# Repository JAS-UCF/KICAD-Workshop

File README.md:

# JAS WORKSHOP - KICAD

The folders in here are the JAS -KiCAD Workshop files for a basic template, the example goes through component selection & wiring

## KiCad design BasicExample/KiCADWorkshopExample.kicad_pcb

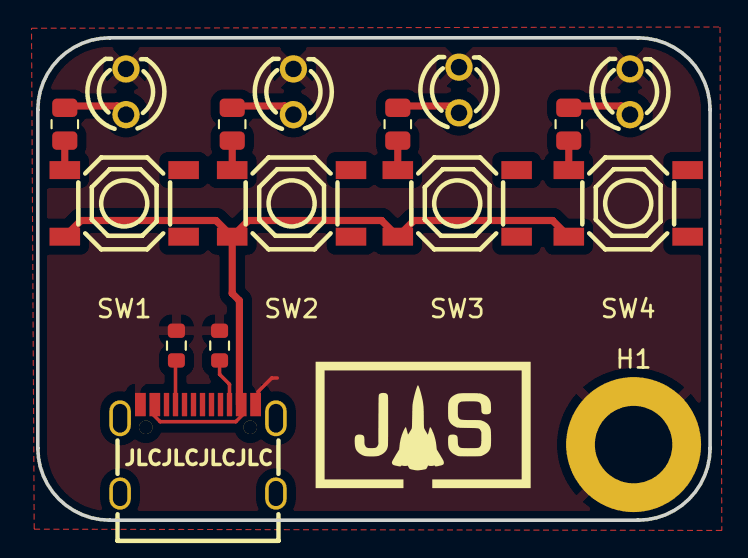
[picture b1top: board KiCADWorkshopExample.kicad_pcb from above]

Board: 2 copper layers, 37.3 x 26.8 mm, 16 parts (0 on the bottom side), 12 nets.

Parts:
H1: MountingHole_Pad; MountingHole_4.3mm_M4_DIN965_Pad
LED1, LED2, LED3, LED4: 204-10SURD/S530-A3-L; LED-TH_BD3.0-P2.54-FD
R1, R2, R3, R4: 120; R_0805_2012Metric
R5, R6: 5K1; R_0603_1608Metric
SW1, SW2, SW3, SW4: TS-1187A-B-A-B; SW-SMD_4P-L5.1-W5.1-P3.70-LS6.5-TL-2
USBC1: TYPE-C-31-M-12; USB-C_SMD-TYPE-C-31-M-12

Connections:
GND: H1.1, LED1.2 (K), LED2.2 (K), LED3.2 (K), LED4.2 (K), R5.2, R6.2, USBC1.A1 (GND), USBC1.A12 (GND), USBC1.B1 (GND), USBC1.B12 (GND)
unnamed: LED1.1 (A), R1.2
unnamed: LED2.1 (A), R2.2
unnamed: LED3.1 (A), R3.2
unnamed: LED4.1 (A), R4.2
unnamed: R4.1, SW1.4 (D)
unnamed: R3.1, SW2.4 (D)
unnamed: R2.1, SW3.4 (D)
unnamed: R1.1, SW4.4 (D)
unnamed: R6.1, USBC1.A5 (CC1)
unnamed: R5.1, USBC1.B5 (CC2)
VBUS: SW1.2 (B), SW2.2 (B), SW3.2 (B), SW4.2 (B), USBC1.A4 (VBUS), USBC1.A9 (VBUS), USBC1.B4 (VBUS), USBC1.B9 (VBUS)

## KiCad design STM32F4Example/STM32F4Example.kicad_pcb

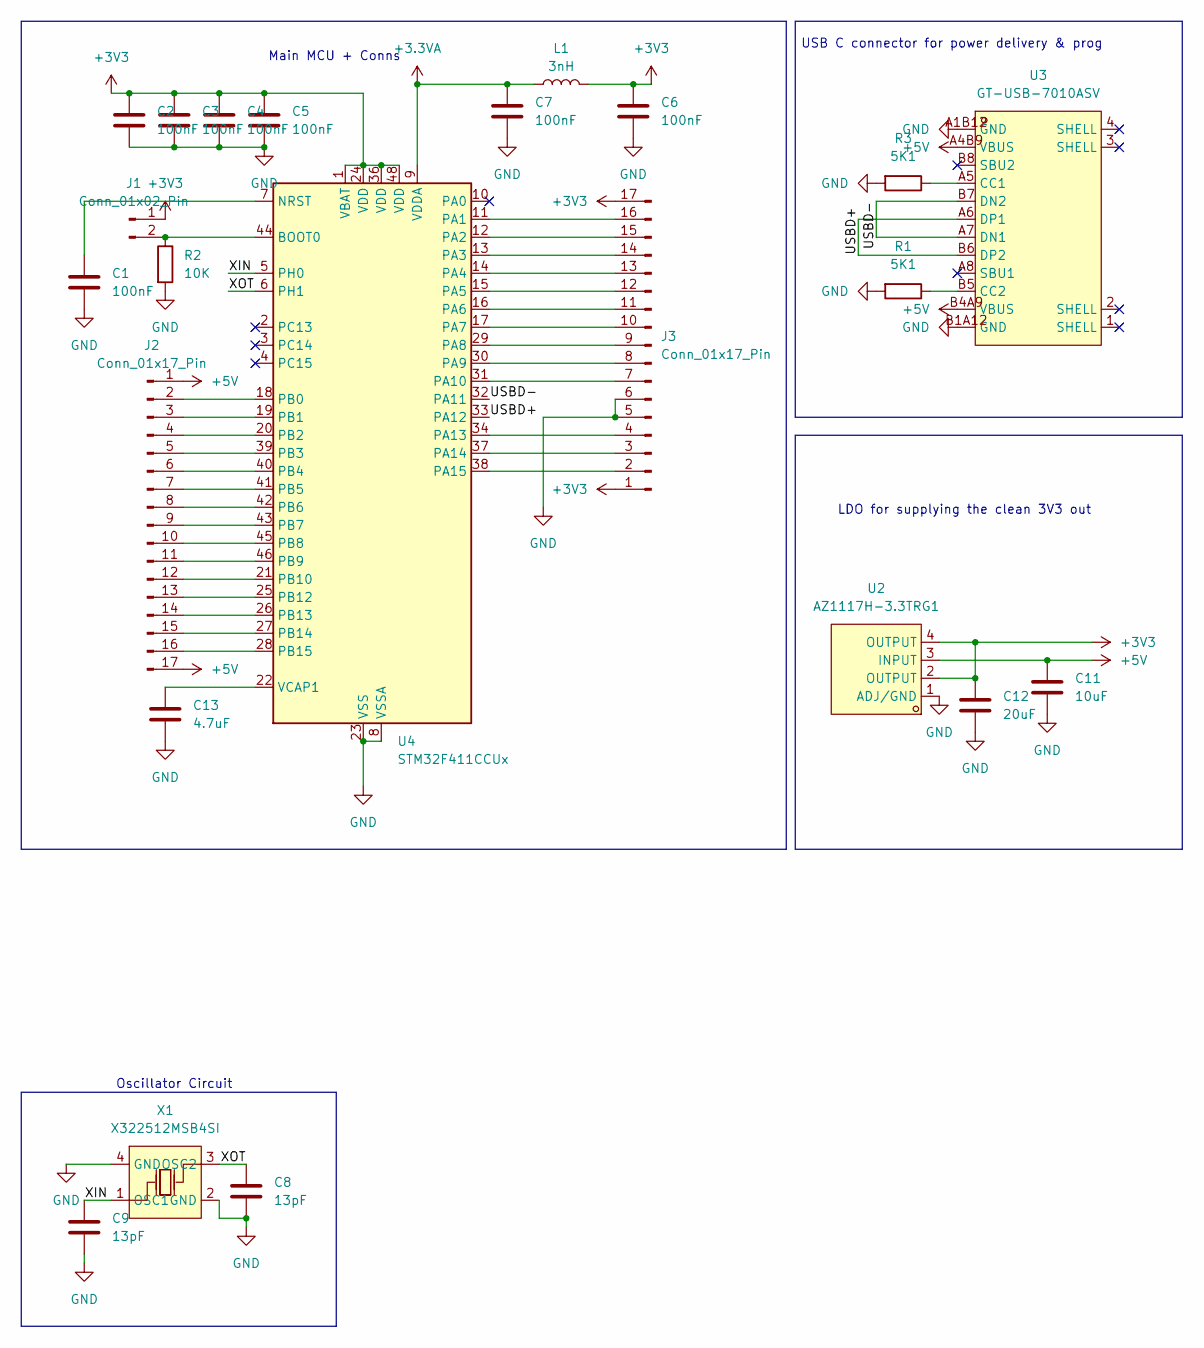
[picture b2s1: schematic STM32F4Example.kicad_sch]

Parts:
C1, C2, C3, C4, C5, C6, C7: 100nF; C_0402_1005Metric
C8, C9: 13pF; C_0402_1005Metric
C11: 10uF; C_0402_1005Metric
C12: 20uF; C_0402_1005Metric
C13: 4.7uF; C_0402_1005Metric
J1: Conn_01x02_Pin; PinHeader_1x02_P2.54mm_Vertical
J2, J3: Conn_01x17_Pin; PinHeader_1x17_P2.54mm_Vertical
L1: 3nH; L_0603_1608Metric
R1, R3: 5K1; R_0603_1608Metric
R2: 10K; R_0603_1608Metric
U2: AZ1117H-3.3TRG1; SOT-223-3_L6.5-W3.4-P2.30-LS7.0-BR; LCSC Part C110474
U3: GT-USB-7010ASV; USB-C-SMD_G-SWITCH_GT-USB-7010ASV; LCSC Part C2988369
U4: STM32F411CCUx; QFN-48-1EP_7x7mm_P0.5mm_EP5.6x5.6mm
X1: X322512MSB4SI; CRYSTAL-SMD_4P-L3.2-W2.5-BL; LCSC Part C9002

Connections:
+3.3VA: C7.1, L1.1, U4.9 (VDDA)
+3V3: C2.1, C3.1, C4.1, C5.1, C6.1, C12.1, J1.1, J3.1, J3.17, L1.2, U2.2 (OUTPUT), U2.4 (OUTPUT), U4.1 (VBAT), U4.24 (VDD), U4.36 (VDD), U4.48 (VDD); also elsewhere on the board
+5V: C11.1, J2.1, J2.17, U2.3 (INPUT), U3.A4B9 (VBUS), U3.B4A9 (VBUS)
/USBD+: U3.A6 (DP1), U3.B6 (DP2), U4.33 (PA12)
/USBD-: U3.A7 (DN1), U3.B7 (DN2), U4.32 (PA11)
/XIN: C9.1, U4.5 (PH0), X1.1 (OSC1)
/XOT: C8.1, U4.6 (PH1), X1.3 (OSC2)
GND: C1.2, C2.2, C3.2, C4.2, C5.2, C6.2, C7.2, C8.2, C9.2, C11.2, C12.2, C13.2, J3.5, J3.6, R1.2, R2.2, R3.2, U2.1 (ADJ/GND), U3.A1B12 (GND), U3.B1A12 (GND), U4.8 (VSSA), U4.23 (VSS), U4.35 (VSS), U4.47 (VSS), U4.49 (VSS), X1.2 (GND), X1.4 (GND); also elsewhere on the board
unnamed: J1.2, R2.1, U4.44 (BOOT0)
unnamed: J2.2, U4.18 (PB0)
unnamed: J2.3, U4.19 (PB1)
unnamed: J2.4, U4.20 (PB2)
unnamed: J2.5, U4.39 (PB3)
unnamed: J2.6, U4.40 (PB4)
unnamed: J2.7, U4.41 (PB5)
unnamed: J2.8, U4.42 (PB6)
unnamed: J2.9, U4.43 (PB7)
unnamed: J2.10, U4.45 (PB8)
unnamed: J2.11, U4.46 (PB9)
unnamed: J2.12, U4.21 (PB10)
unnamed: J2.13, U4.25 (PB12)
unnamed: J2.14, U4.26 (PB13)
unnamed: J2.15, U4.27 (PB14)
unnamed: J2.16, U4.28 (PB15)
unnamed: J3.2, U4.38 (PA15)
unnamed: J3.3, U4.37 (PA14)
unnamed: J3.4, U4.34 (PA13)
unnamed: J3.7, U4.31 (PA10)
unnamed: J3.8, U4.30 (PA9)
unnamed: J3.9, U4.29 (PA8)
unnamed: J3.10, U4.17 (PA7)
unnamed: J3.11, U4.16 (PA6)
unnamed: J3.12, U4.15 (PA5)
unnamed: J3.13, U4.14 (PA4)
unnamed: J3.14, U4.13 (PA3)
unnamed: J3.15, U4.12 (PA2)
unnamed: J3.16, U4.11 (PA1)
unnamed: R3.1, U3.A5 (CC1)
unnamed: R1.1, U3.B5 (CC2)
unnamed: C1.1, U4.7 (NRST)
unnamed: C13.1, U4.22 (VCAP1)

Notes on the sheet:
Main MCU + Conns
LDO for supplying the clean 3V3 out
Oscillator Circuit
USB C connector for power delivery & prog

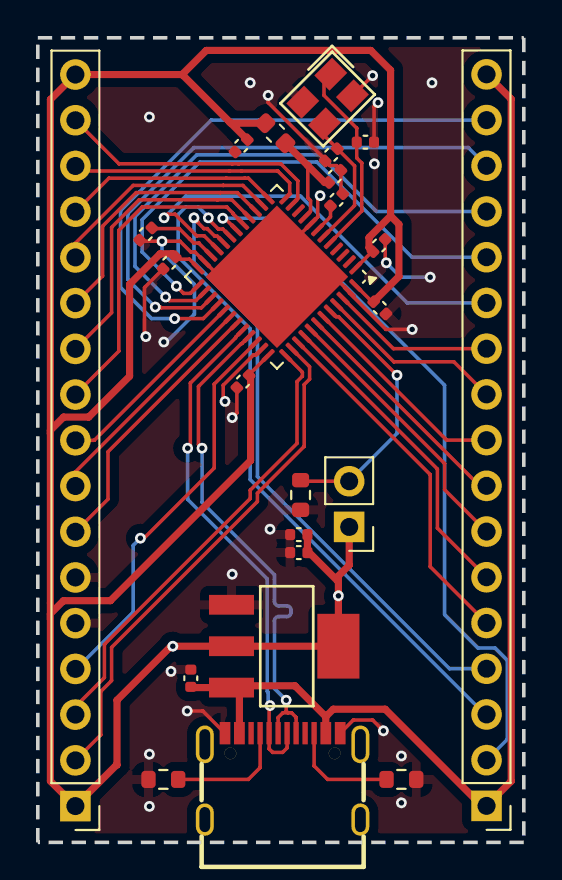
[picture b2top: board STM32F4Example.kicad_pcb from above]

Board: 2 copper layers, 27.0 x 44.7 mm, 24 parts (0 on the bottom side), 41 nets.

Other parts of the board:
C10: 10uF; C_0402_1005Metric

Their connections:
+3V3: C10.1; also elsewhere on the board
GND: C10.2; also elsewhere on the board

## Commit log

2024-08-23 first workshop files BASIC
2024-08-25 re-format dir
2024-10-13 complete simple tut
2024-10-17 sets up generic schematic missing proper module && usbc footprint
2024-10-18 traces
2024-10-18 Create static.yml for STM32F4Example
2024-10-19 new switch & board in production
